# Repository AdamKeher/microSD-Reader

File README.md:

# microSD Card Reader
An SPI controlled microSD card reader with builtin status LED and push/push card mechanism and card detect.
## PCB Layout

## Features
* 3.3v tolerant
* microSD card reader with push/push mechanism for easy ejection
* Status LED on clock line and enabled when CS selected / low
* Breadboard friendly
* Compatible With Most Microcontrollers
* Card detection pin
* Pull up resistor on CS
* Decoupling caps on SD card
* Option to add pulldown's on MOSI and MISO lines if required.

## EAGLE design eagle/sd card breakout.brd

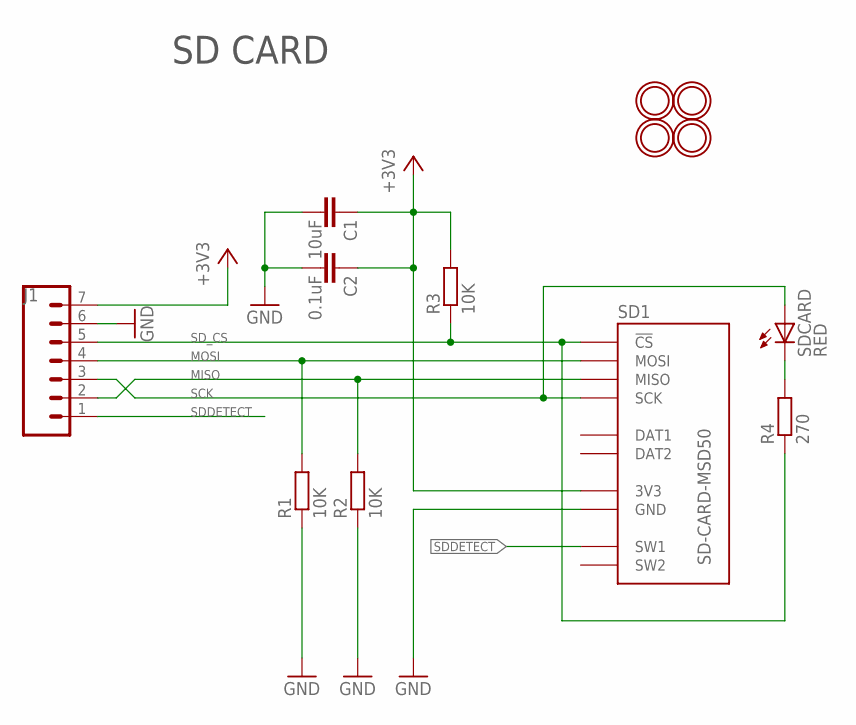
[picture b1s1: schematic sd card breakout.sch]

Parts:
C1: 10uF; C0805K
C2: 0.1uF; C0805K
J1: CONN_07NO_SILK; 1X07_NO_SILK
MH1, MH2, MH3, MH4: MOUNTINGHOLE2.5; MOUNTINGHOLE_2.5_PLATED
R1, R2, R3: 10K; R0805
R4: 270; R0805
SD1: SD-CARD-MSD50; SD_5031821853
SDCARD: RED; CHIP-LED0805

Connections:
+3V3: C1.1, C2.1, J1.7, R3.2, SD1.VCC (3V3)
GND: C1.2, C2.2, J1.6, R1.1, R2.1, SD1.GND
MISO: J1.2, R2.2, SD1.MISO
MOSI: J1.4, R1.2, SD1.MOSI
unnamed: R4.2, SDCARD.C
SCK: J1.3, SD1.SCK, SDCARD.A
SDDETECT: J1.1, SD1.SW1
SD_CS: J1.5, R3.1, R4.1, SD1.CS (!CS)

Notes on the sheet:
SD CARD

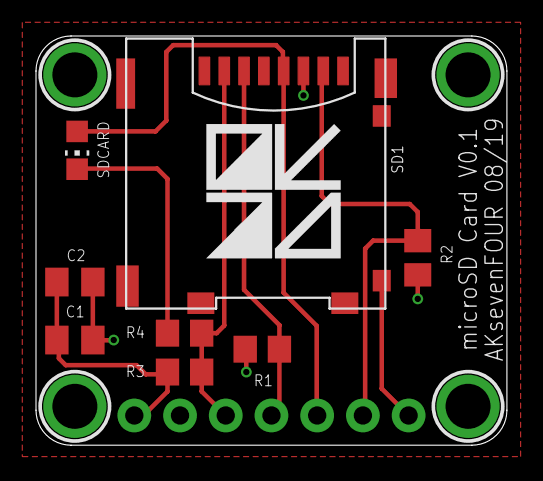
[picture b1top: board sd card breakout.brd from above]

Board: 2 copper layers, 26.2 x 22.7 mm, 15 parts (1 on the bottom side), 8 nets.

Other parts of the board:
U$1: AK74_LOGO_MEDIUM
U$2: AK74_LOGO_MEDIUM_TEXTONLY_SQUARE

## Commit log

2019-09-14 Image Update

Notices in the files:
parts and their libraries:
SparkFun-Connectors: Licensing: Creative Commons ShareAlike 4.0 International - https://creativecommons.org/licenses/by-sa/4.0
microbuilder: This work is placed in the public domain, and may be freely used for commercial and non-commercial work with the following conditions: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
